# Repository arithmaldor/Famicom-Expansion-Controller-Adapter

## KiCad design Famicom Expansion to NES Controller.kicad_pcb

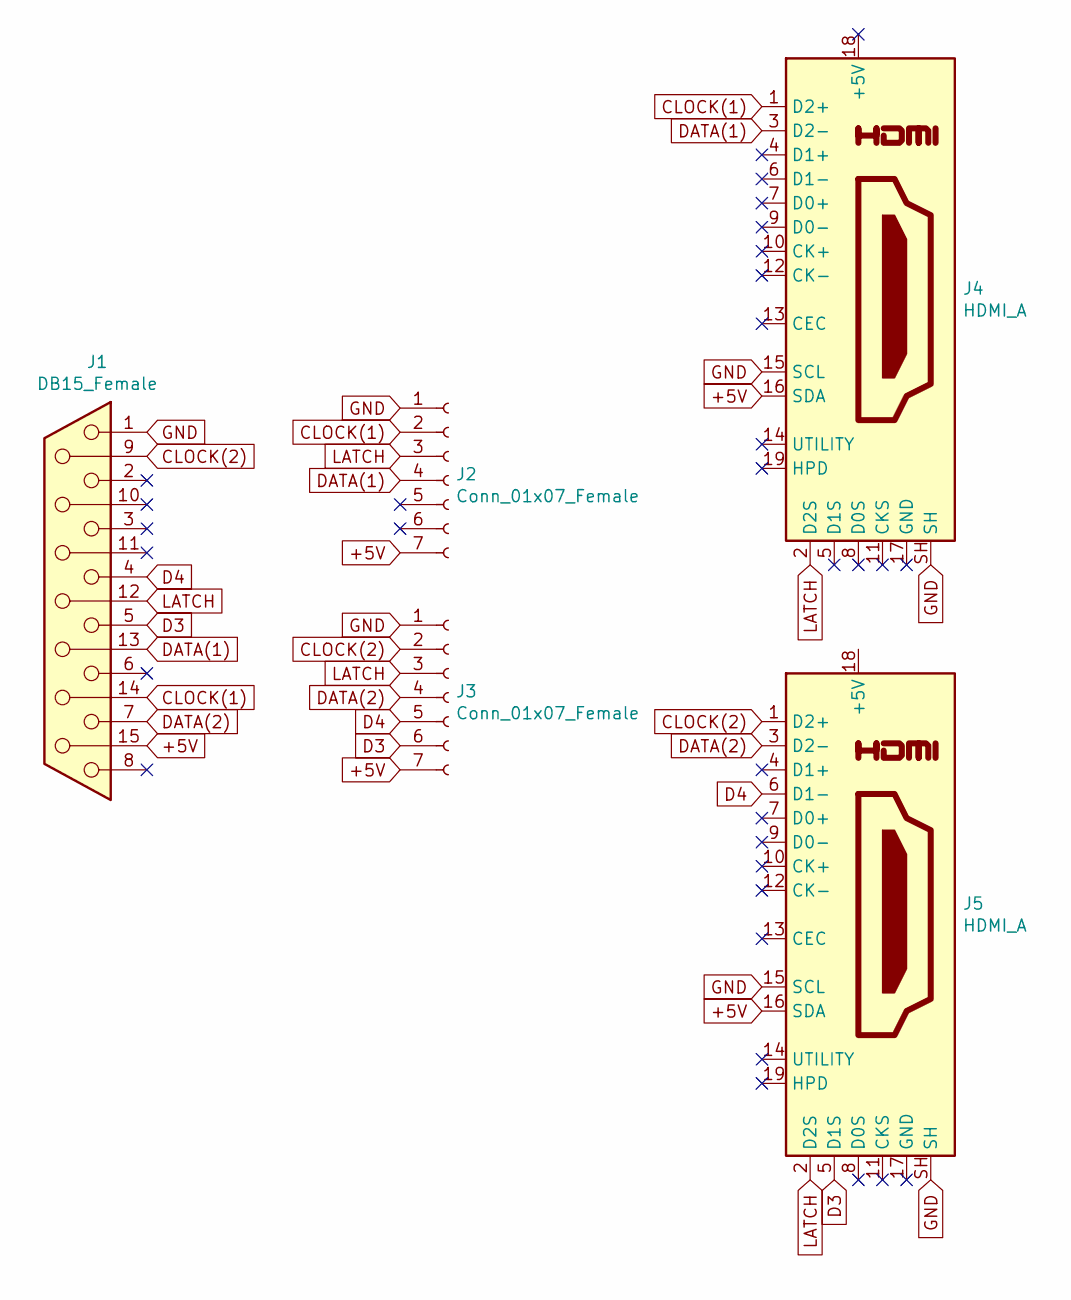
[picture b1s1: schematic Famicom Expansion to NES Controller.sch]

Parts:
J1: DB15_Female; DSUB-15_Female_Vertical_P2.77x2.84mm
J2, J3: Conn_01x07_Female; NES_CONTROLLER_VERT
J4, J5: HDMI_A; HDMI_VERT_47659-1000

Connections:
+5V: J1.15, J2.7, J3.7, J4.16 (SDA), J5.16 (SDA)
CLOCK(1): J1.14, J2.2, J4.1 (D2+)
CLOCK(2): J1.9, J3.2, J5.1 (D2+)
D3: J1.5, J3.6, J5.5 (D1S)
D4: J1.4, J3.5, J5.6 (D1-)
DATA(1): J1.13, J2.4, J4.3 (D2-)
DATA(2): J1.7, J3.4, J5.3 (D2-)
GND: J1.1, J2.1, J3.1, J4.15 (SCL), J4.SH, J5.15 (SCL), J5.SH
LATCH: J1.12, J2.3, J3.3, J4.2 (D2S), J5.2 (D2S)

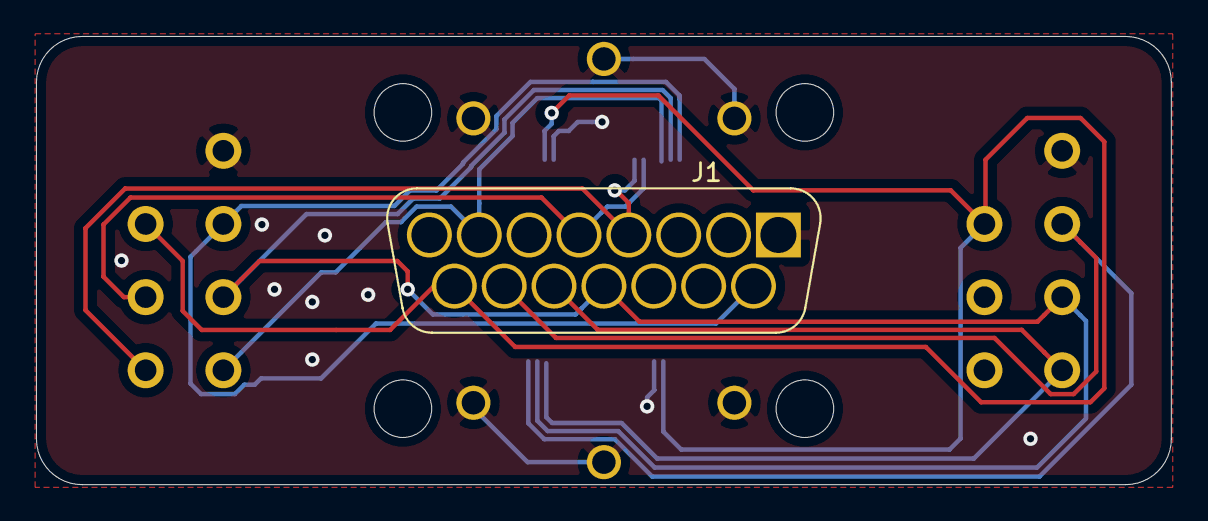
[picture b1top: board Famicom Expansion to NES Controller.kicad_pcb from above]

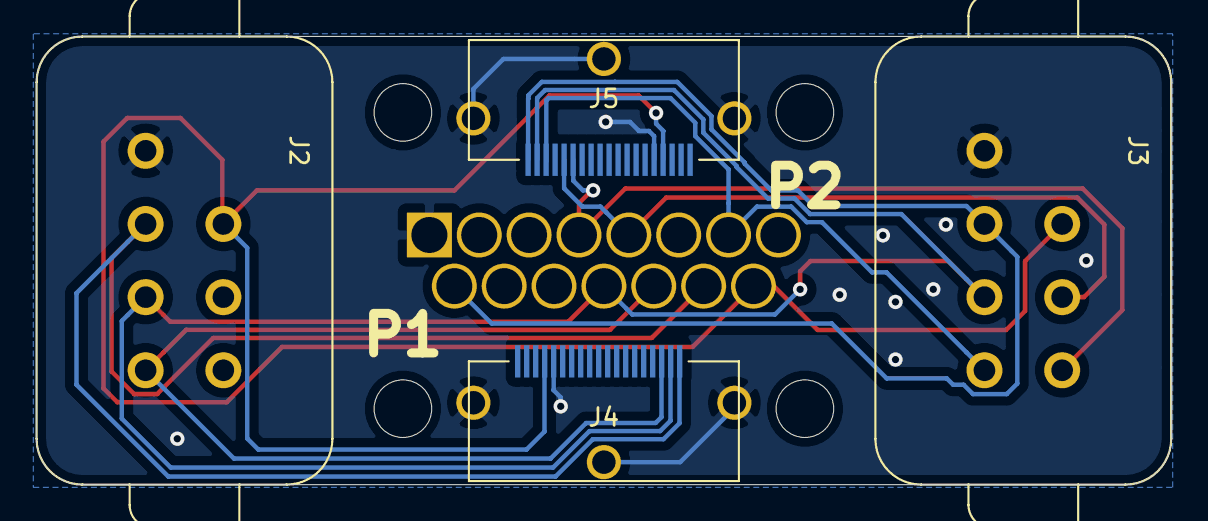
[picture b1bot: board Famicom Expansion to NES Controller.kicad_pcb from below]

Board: 2 copper layers, 63.1 x 24.9 mm, 5 parts (4 on the bottom side), 9 nets.

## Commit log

2019-07-31 Added folder to begin adding HDMI ports
2019-08-18 added datasheet for reference
2019-08-18 Added HDMI Ports for Blissbox compatibility
2019-10-24 not sure what changes I made
